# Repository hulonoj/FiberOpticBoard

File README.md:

# Fiber Optic Based Signal Extender

A high-speed hardware system designed to transmit and replicate electrical signals over long distances using fiber optics with minimal latency.

## Overview

This project consists of two custom PCB systems designed for high-speed signal replication across fiber:

- **Transmitter/Receiver Board:** FPGA-based PCB for protocol-agnostic electrical signal replication over fiber with ~30 ns latency.
- **Motor Controller Board:** STM32-based H-Bridge driver interfaced via I2C through the fiber optic system.

The design demonstrates a full end-to-end communication system without electrical coupling, ideal for applications where noise isolation or long-distance communication is required. This was my capstone project for my Advanced Embedded Systems course at the University of Michigan, and was worked on by a team of five. I contributed heavily and mainly to the hardware development and testing, while collaborating closely with teammates on software and system integration and validation.

## Features

- Custom fiber optic communication protocol with latency < 30 ns
- Supports arbitrary digital signal formats (protocol-agnostic)
- Isolated end-to-end data replication
- STM32 motor controller with I2C command input
- Integrated H-Bridge for direct motor control

## Photos

Fiber Optic Board mounted on top of a motor controller board.

Half-Assembled Fiber Optic Board

Schematic

Layout

## Poster Describing Project

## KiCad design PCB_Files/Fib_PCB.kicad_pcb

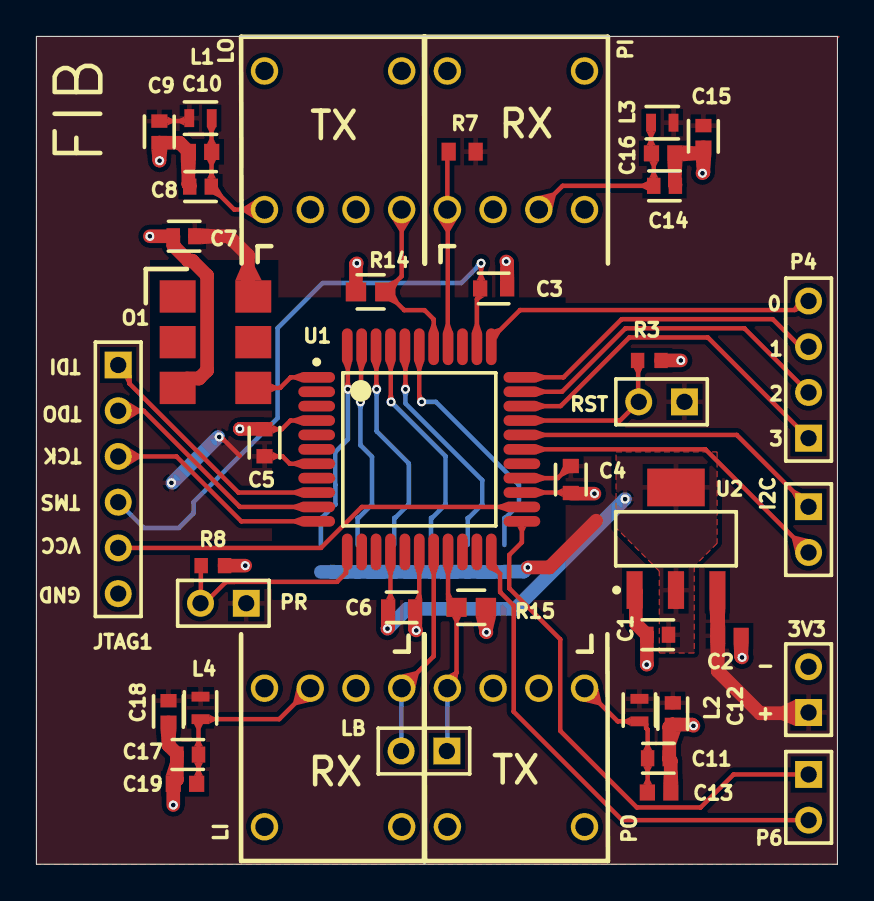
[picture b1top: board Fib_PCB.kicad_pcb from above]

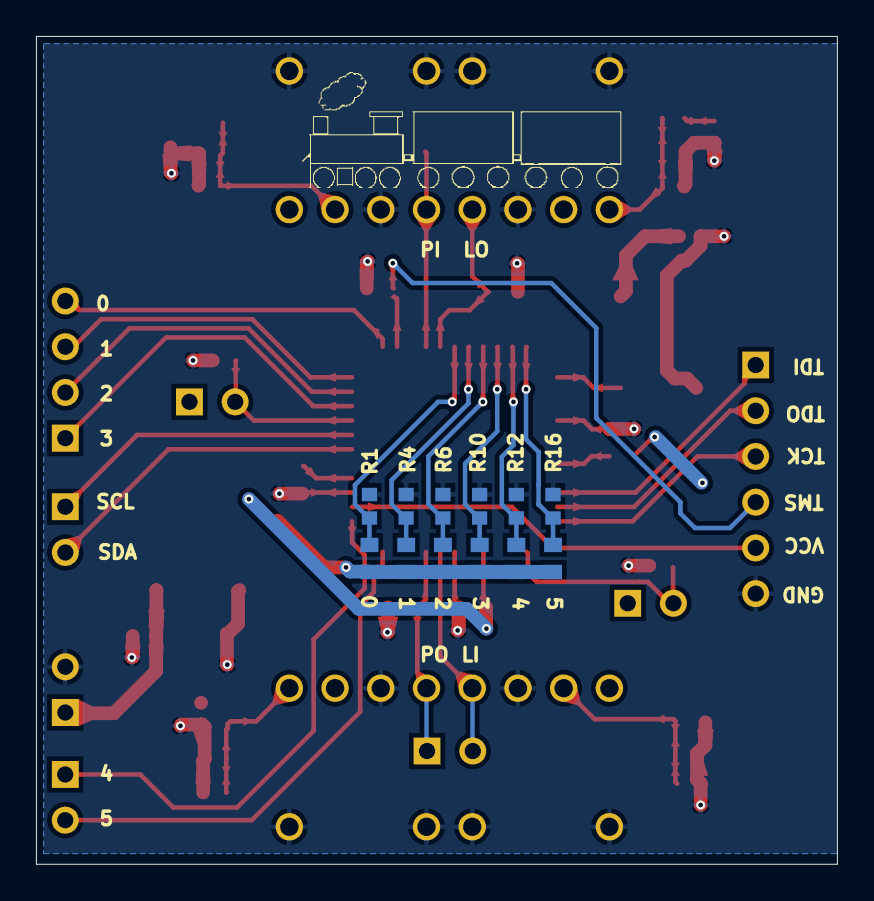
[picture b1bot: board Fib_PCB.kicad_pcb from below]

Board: 2 copper layers, 44.5 x 46.0 mm, 55 parts (12 on the bottom side), 33 nets.

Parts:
0, 1, 2, 3, 4, 5: RC0603JR-070RL; RESC1608X55X25ML10T15
3V3: Header 2; HDR1X2
C1, C7, C8, C9, C11, C12, C14, C15, C17, C18: 10uF 0603; FP-C0603C106M9PACTU-MFG
C2, C10, C13, C16, C19: 100nF 0603; CAPC1608X90X35LL15T15
C3, C4, C5, C6: CC0603KRX7R7BB104; FP-CC0603-DA-MFG
I2C: Header 2; HDR1X2
JTAG1: Header 6; HDR1X6
L1, L2, L3, L4: 1uH; FP-LBMF1608-0_8-0_2-MFG
LB: Header 2; HDR1X2
LI: RX; PCBComponent_1
LO: TX; PCBComponent_1
O1: Oscillator
P4: Header 4; HDR1X4
P6: Header 2; HDR1X2
PI: RX; PCBComponent_1
PO: TX; PCBComponent_1
PR: Header 2; HDR1X2
R1, R3, R4, R6, R8, R10, R12, R16: ERJ3EKF1002V; RESC1609X55X30LL15T15
R7: RC0603JR-070RL; RESC1608X55X25ML10T15
R14, R15: 4.7k 0603; FP-CRCW0603-e3-IPC_A
RST: Header 2; HDR1X2
U1: XC2C64A-5VQG44C; VQG44_M
U2: LD1117AS18TR; SOT-223_L

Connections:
250MHz: O1.4, U1.1
+1.8V: C1.1, C6.1, U1.15, U2.2, U2.4
+3.3: 0.2, 1.2, 2.2, 3.2, 3V3.1, 4.2, 5.2, C2.2, C4.1, C5.1, C7.1, C9.1, C12.1, C15.1, C18.1, L1.2, L2.2, L3.2, L4.2, O1.6, PR.1, R7.2, RST.1, U1.7, U1.26, U2.3
GND: 3V3.2, C1.2, C2.1, C3.2, C4.2, C5.2, C6.2, C7.2, C8.2, C9.2, C10.1, C11.2, C12.2, C13.1, C14.2, C15.2, C16.1, C17.2, C18.2, C19.1, JTAG1.6, LI.2, LI.5, LI.8, LO.3, LO.5, LO.8, O1.3, PI.2, PI.5, PI.8, PO.3, PO.5, PO.8, R1.1, R3.1, R4.1, R6.1, R8.1, R10.1, R12.1, R14.1, R15.1, R16.1, U1.4, U1.17, U1.25, U2.1
GPIO0: P4.4, U1.34
GPIO1: P4.3, U1.33
GPIO2: P4.2, U1.32
GPIO3: P4.1, U1.31
GPIO4: P6.1, U1.23
GPIO5: P6.2, U1.22
JTAG_VCC: C3.1, JTAG1.4, U1.35
LI: LB.2, LI.1, U1.18
LO: LO.4, R14.2, U1.38
NetC8_1: C8.1, C10.2, L1.1, LO.1
NetC11_1: C11.1, C13.2, L2.1, PO.1
NetC14_1: C14.1, C16.2, L3.1, PI.3
NetC17_1: C17.1, C19.2, L4.1, LI.3
PI: PI.1, R7.1, U1.37
PO: LB.1, PO.4, R15.2, U1.19
Reset: R3.2, RST.2, U1.30
SCL: I2C.1, U1.29
SDA: I2C.2, U1.28
SEL0: 0.1, R1.2, U1.39
SEL1: 1.1, R4.2, U1.40
SEL2: 2.1, R6.2, U1.41
SEL3: 3.1, R10.2, U1.42
SEL4: 4.1, R12.2, U1.43
SEL5: 5.1, R16.2, U1.44
TCK: JTAG1.3, U1.11
TDI: JTAG1.1, U1.9
TDO: JTAG1.5, U1.24
TMS: JTAG1.2, U1.10
i2c_mode: PR.2, R8.2, U1.12

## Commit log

2025-05-27 Init Commit
2025-05-27 Add readme
2025-05-29 add 473 poster to README
2025-05-30 Update readme with my contribution
